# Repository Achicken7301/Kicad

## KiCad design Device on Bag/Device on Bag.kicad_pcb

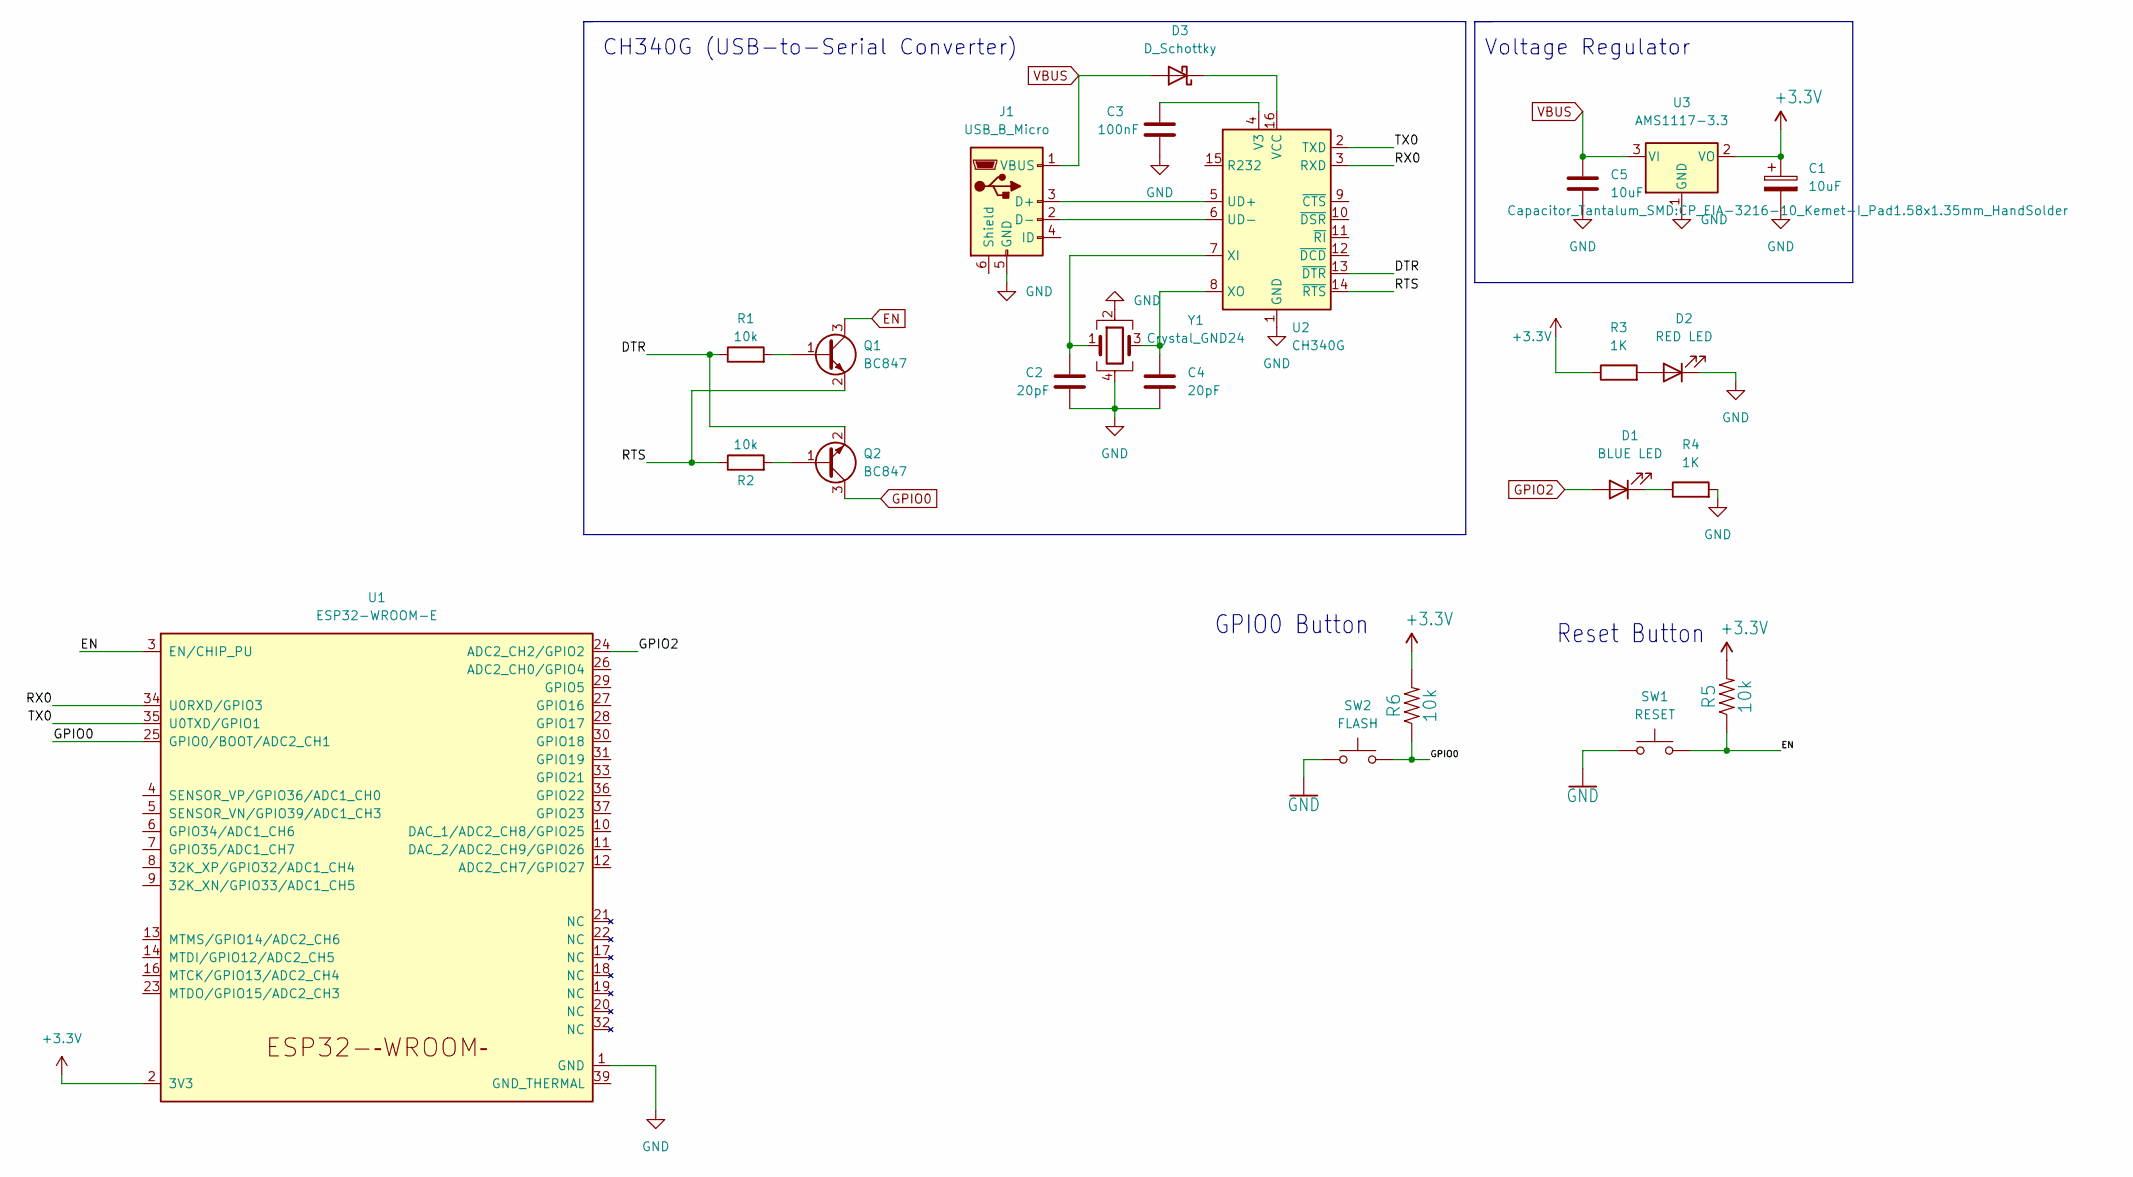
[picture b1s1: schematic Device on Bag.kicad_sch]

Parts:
C1: 10uF; CP_EIA-3216-10_Kemet-I_Pad1.58x1.35mm_HandSolder
C2, C4: 20pF; C_0805_2012Metric_Pad1.18x1.45mm_HandSolder
C3: 100nF; C_0805_2012Metric_Pad1.18x1.45mm_HandSolder
C5: 10uF; C_0805_2012Metric_Pad1.18x1.45mm_HandSolder
D1: BLUE LED; LED_0805_2012Metric_Pad1.15x1.40mm_HandSolder
D2: RED LED; LED_0805_2012Metric_Pad1.15x1.40mm_HandSolder
D3: D_Schottky; D_SMA_Handsoldering
J1: USB_B_Micro; USB_Micro-B_Molex-105017-0001
Q1, Q2: BC847; SOT-23
R1, R2, R5, R6: 10k; R_0805_2012Metric_Pad1.20x1.40mm_HandSolder
R3, R4: 1K; R_0805_2012Metric_Pad1.20x1.40mm_HandSolder
SW1: RESET; SW_Push_SPST_NO_Alps_SKRK
SW2: FLASH; SW_Push_SPST_NO_Alps_SKRK
U1: ESP32-WROOM-E; ESP32-WROOM-32E
U2: CH340G; SOIC-16_3.9x9.9mm_P1.27mm
U3: AMS1117-3.3; SOT-223-3_TabPin2
Y1: Crystal_GND24; Crystal_SMD_5032-4Pin_5.0x3.2mm

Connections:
/DTR: Q2.2 (E), R1.1, U2.13 (~DTR)
/RTS: Q1.2 (E), R2.1, U2.14 (~RTS)
/RX0: U1.34 (U0RXD/GPIO3), U2.3 (RXD)
/TX0: U1.35 (U0TXD/GPIO1), U2.2 (TXD)
EN: Q1.3 (C), R5.1, SW1.2, U1.3 (EN/CHIP_PU)
GND: C1.2, C2.2, C3.2, C4.2, C5.2, D2.1 (K), J1.5 (GND), R4.2, SW1.1, SW2.1, U1.1 (GND), U1.15 (GND), U1.38 (GND), U2.1 (GND), U3.1 (GND), Y1.2, Y1.4
GPIO0: Q2.3 (C), R6.1, SW2.2, U1.25 (GPIO0/BOOT/ADC2_CH1)
GPIO2: D1.2 (A), U1.24 (ADC2_CH2/GPIO2)
unnamed: C2.1, U2.7 (XI), Y1.1
unnamed: C3.1, U2.4 (V3)
unnamed: C4.1, U2.8 (XO), Y1.3
unnamed: D1.1 (K), R4.1
unnamed: D2.2 (A), R3.2
unnamed: D3.1 (K), U2.16 (VCC)
unnamed: J1.2 (D-), U2.6 (UD-)
unnamed: J1.3 (D+), U2.5 (UD+)
unnamed: Q1.1 (B), R1.2
unnamed: Q2.1 (B), R2.2
VBUS: C5.1, D3.2 (A), J1.1 (VBUS), U3.3 (VI)

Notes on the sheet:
Reset Button
GPIO0 Button
CH340G (USB-to-Serial Converter)
Voltage Regulator

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
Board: 2 copper layers, 23 parts (0 on the bottom side), 21 nets, no tracks yet.

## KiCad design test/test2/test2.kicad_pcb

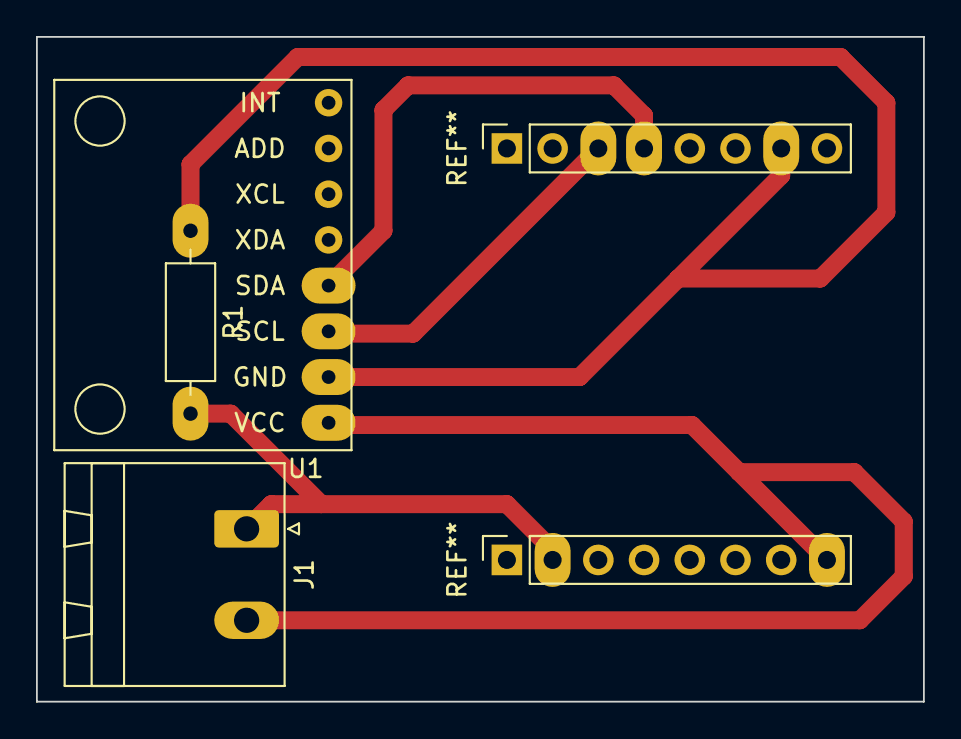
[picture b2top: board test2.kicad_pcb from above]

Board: 2 copper layers, 49.3 x 36.9 mm, 3 parts (0 on the bottom side), 3 nets.

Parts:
J1: Screw_Terminal_01x02; PhoenixContact_MSTBA_2,5_2-G-5,08_1x02_P5.08mm_Horizontal
R1: R; R_Axial_DIN0207_L6.3mm_D2.5mm_P10.16mm_Horizontal
U1: module_mpu6050

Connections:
3v3: J1.2, U1.1 (VCC)
unnamed: J1.1, R1.2
gnd: R1.1, U1.2 (GND)

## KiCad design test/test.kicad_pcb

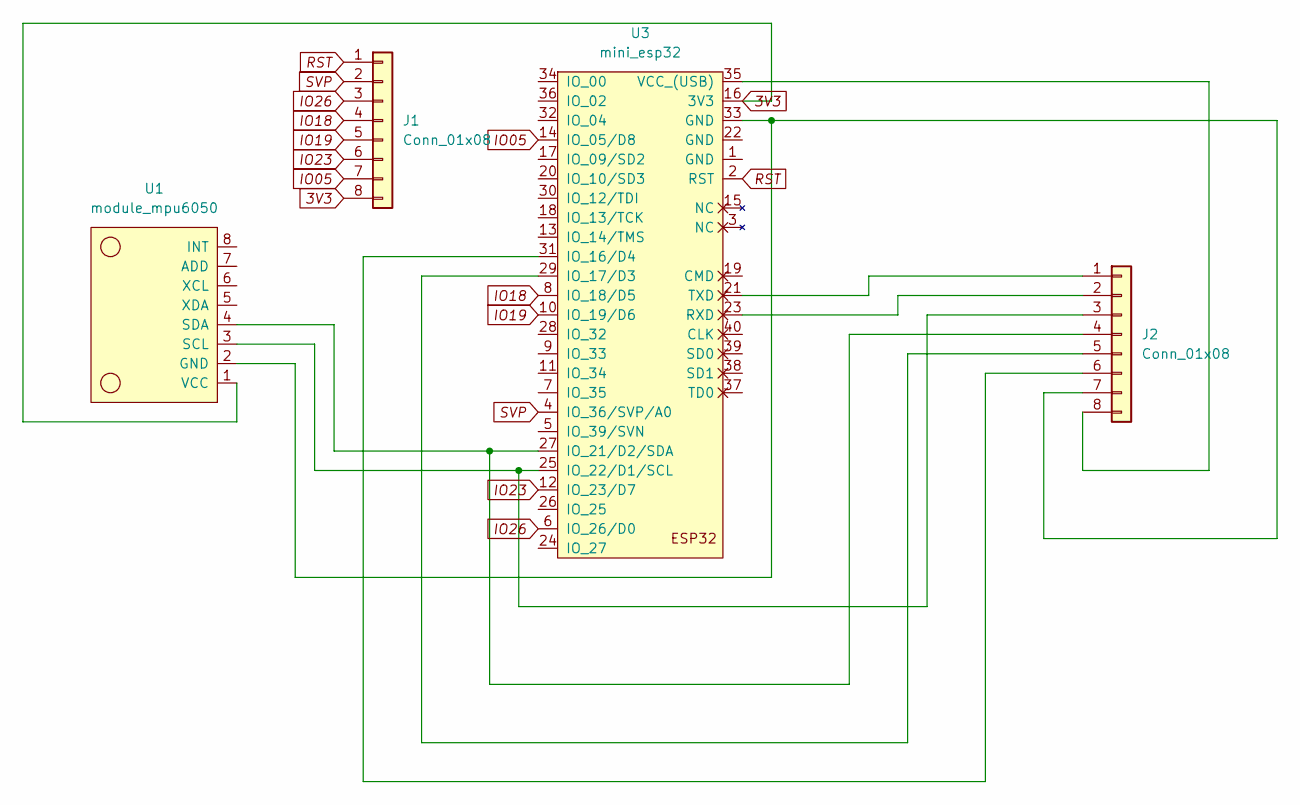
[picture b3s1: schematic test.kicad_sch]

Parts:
J1, J2: Conn_01x08; PinSocket_1x08_P2.54mm_Vertical
U1: module_mpu6050
U3: mini_esp32; ESP32_mini

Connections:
3V3: J1.8, U1.1 (VCC), U3.16 (3V3)
IO05: J1.7, U3.14 (IO_05/D8)
IO18: J1.4, U3.8 (IO_18/D5)
IO19: J1.5, U3.10 (IO_19/D6)
IO23: J1.6, U3.12 (IO_23/D7)
IO26: J1.3, U3.6 (IO_26/D0)
unnamed: J2.1, U3.21 (TXD)
unnamed: J2.2, U3.23 (RXD)
unnamed: J2.3, U1.3 (SCL), U3.25 (IO_22/D1/SCL)
unnamed: J2.4, U1.4 (SDA), U3.27 (IO_21/D2/SDA)
unnamed: J2.5, U3.29 (IO_17/D3)
unnamed: J2.6, U3.31 (IO_16/D4)
unnamed: J2.7, U1.2 (GND), U3.33 (GND)
unnamed: J2.8, U3.35 (VCC_(USB))
RST: J1.1, U3.2 (RST)
SVP: J1.2, U3.4 (IO_36/SVP/A0)

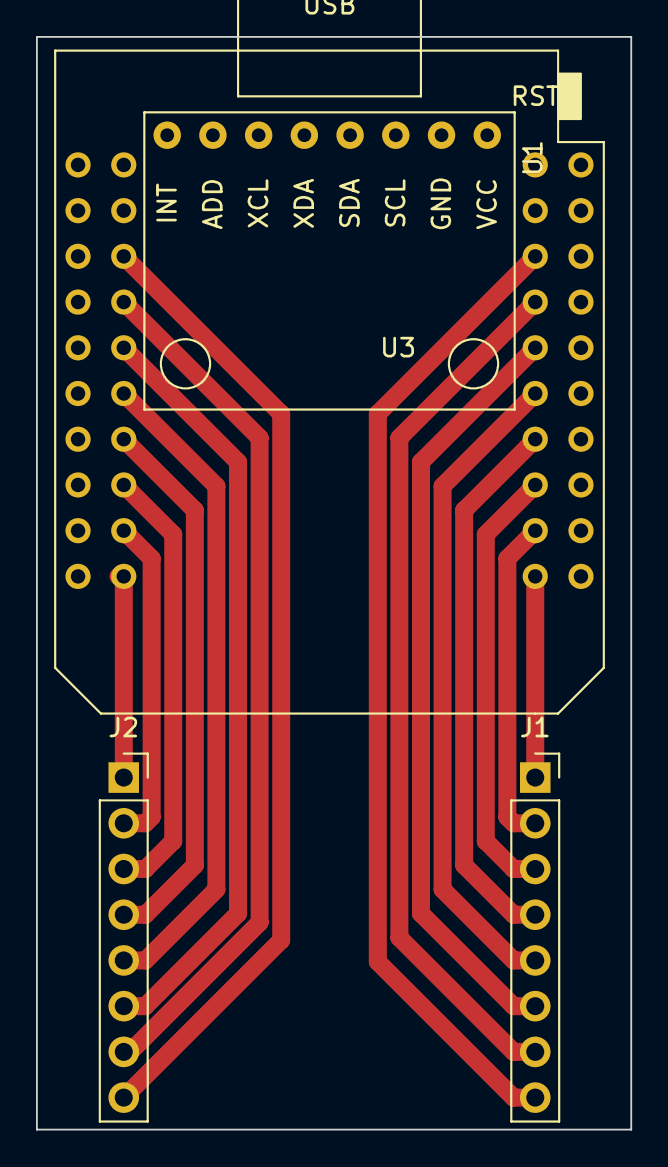
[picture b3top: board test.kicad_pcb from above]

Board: 2 copper layers, 33.0 x 60.7 mm, 4 parts (0 on the bottom side), 16 nets.

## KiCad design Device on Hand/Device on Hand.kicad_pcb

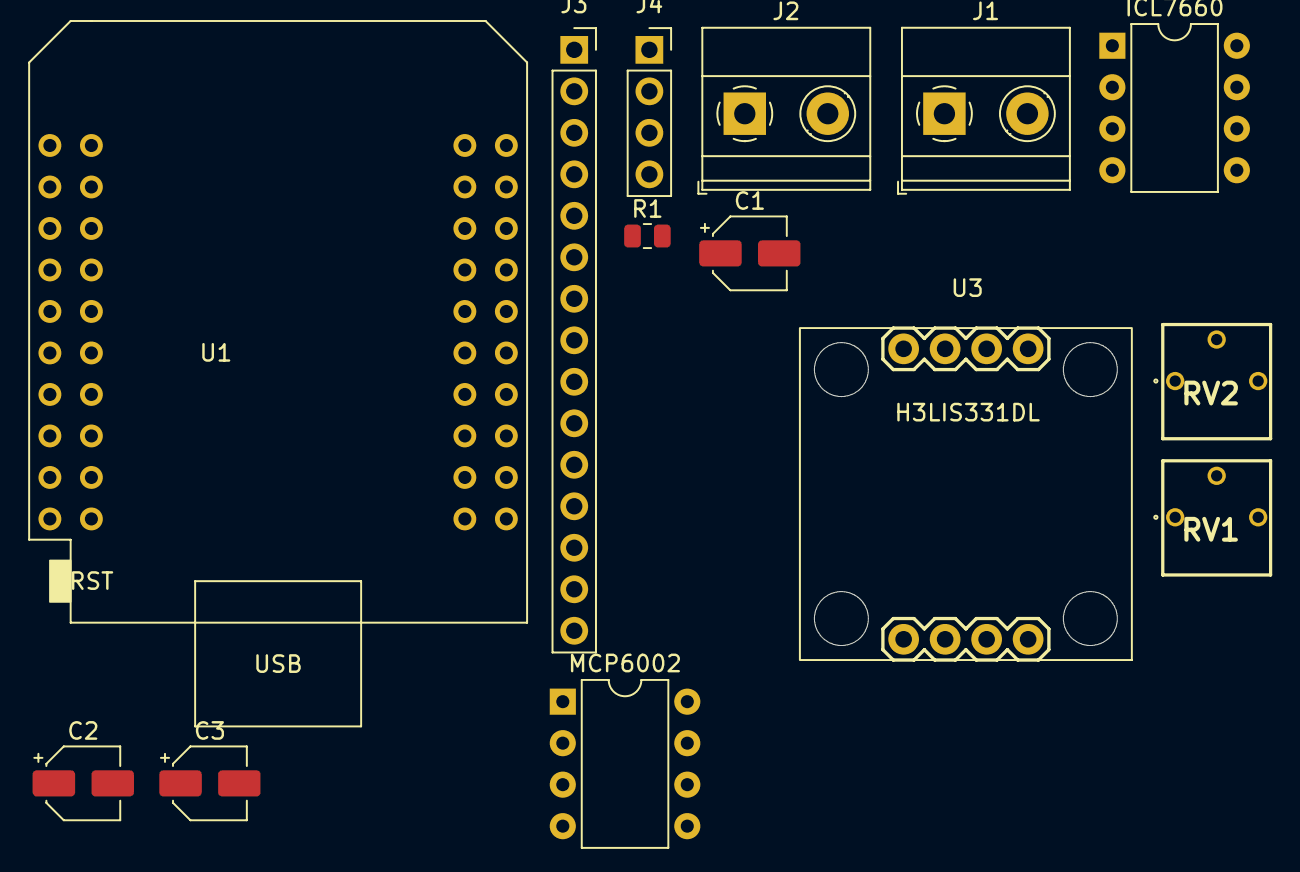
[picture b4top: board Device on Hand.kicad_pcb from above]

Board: 2 copper layers, 14 parts (0 on the bottom side), 13 nets, no tracks yet.

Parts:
C1, C2: 10uF_10V_Polarized_US; CP_Elec_4x4.5
C3: 47uF_10V_Polarized_US; CP_Elec_4x4.5
ICL7660: ICL7660; DIP-8_W7.62mm
J1, J2: Screw_Terminal_01x02; TerminalBlock_Phoenix_MKDS-1,5-2-5.08_1x02_P5.08mm_Horizont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
J3: Conn_01x15; PinSocket_1x15_P2.54mm_Vertical
J4: Screw_Terminal_01x04; PinSocket_1x04_P2.54mm_Vertical
MCP6002: MCP6002-xMC; DIP-8_W7.62mm
R1: 1k; R_0805_2012Metric
RV1: 20k_Potentiometer; 3362P_1
RV2: 100k_Potentiometer; 3362P_1
U1: mini_esp32; ESP32_mini
U3: SparkFun_SEN-14480_H3LIS331DL; SparkFun_Tri_Axis_Accel_Breakout-H3LIS331DL

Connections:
3.3Vin: J2.1, U1.35 (VCC_(USB))
3.3v: MCP6002.8 (V+), U1.16 (3V3), U3.3 (3.3V)
CS: U1.14 (IO_05/D8), U3.8 (CS)
GND: C2.1, ICL7660.3 (GND), J2.2, MCP6002.3 (+), MCP6002.4 (V-), R1.2, U1.33 (GND), U3.4 (GND)
MISO: U1.10 (IO_19/D6), U3.7 (SA0)
MOSI: U1.12 (IO_23/D7), U3.2 (SDA)
unnamed: C1.1, ICL7660.2 (CAP+)
unnamed: C1.2, ICL7660.4 (CAP-)
unnamed: C2.2, ICL7660.5 (VOUT), RV1.1
unnamed: C3.2, J1.2, MCP6002.2 (-), RV2.1
unnamed: J1.1, R1.1, RV1.2
SCL: U1.8 (IO_18/D5), U3.1 (SCL)
Vout: C3.1, MCP6002.1, RV2.2, U1.6 (IO_26/D0)

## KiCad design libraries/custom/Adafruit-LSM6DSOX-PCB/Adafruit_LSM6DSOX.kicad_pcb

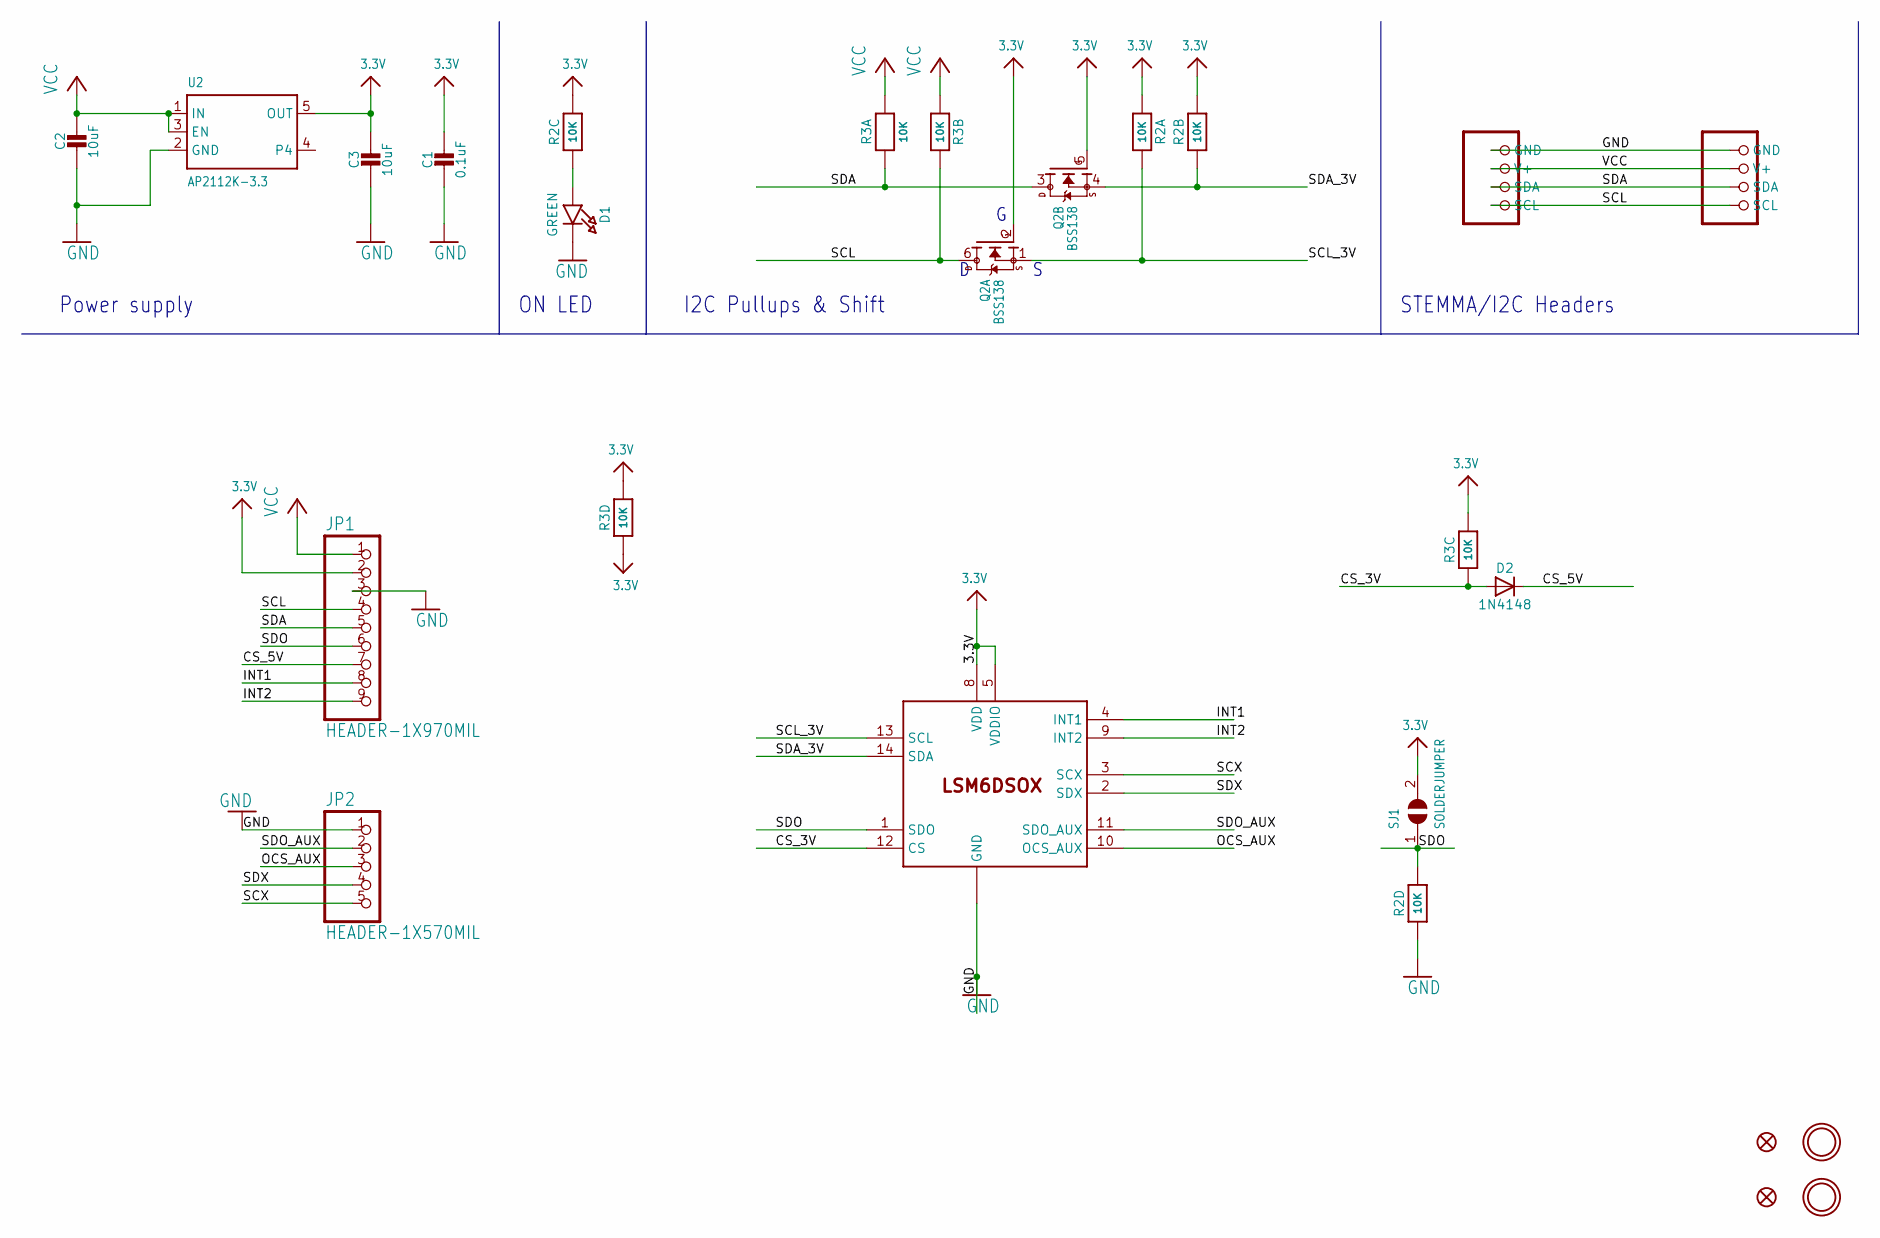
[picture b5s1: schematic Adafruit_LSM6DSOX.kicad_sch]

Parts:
C1: 0.1uF; 0603-NO
C2, C3: 10uF; 0805-NO
CONN3, CONN4: STEMMA_I2C_QT; JST_SH4
D1: GREEN; CHIPLED_0603_NOOUTLINE
D2: 1N4148; SOD-323
FID3, FID4: FIDUCIAL_1MM
JP1: HEADER-1X970MIL; 1X09_ROUND_70
JP2: HEADER-1X570MIL; 1X05_ROUND_70
Q2: BSS138; SOT363
R2, R3: 10K; RESPACK_4X0603
SJ1: SOLDERJUMPER; SOLDERJUMPER_ARROW_NOPASTE
U2: AP2112K-3.3; SOT23-5
U$1, U$17: MOUNTINGHOLE2.5; MOUNTINGHOLE_2.5_PLATED
U$2: LSM6DSOX; LGA-14L

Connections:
3.3V: C1.1, C3.1, JP1.2, Q2.2 (G), Q2.5 (G), R2.1, R2.2 (1), R2.6 (2), R3.3 (1), R3.4 (1), R3.5 (2), SJ1.2, U2.5 (OUT), U$2.5 (VDDIO), U$2.8 (VDD)
CS_3V: D2.A, R3.6 (2), U$2.12 (CS)
CS_5V: D2.C, JP1.7
GND: C1.2, C2.2, C3.2, CONN3.1 (GND), CONN4.1 (GND), D1.C, JP1.3, JP2.1, R2.4 (1), U2.2 (GND), U$2.6 (GND), U$2.7 (GND)
INT1: JP1.8, U$2.4 (INT1)
INT2: JP1.9, U$2.9 (INT2)
unnamed: D1.A, R2.3 (1)
OCS_AUX: JP2.3, U$2.10 (OCS_AUX)
SCL: CONN3.4 (SCL), CONN4.4 (SCL), JP1.4, Q2.6 (D), R3.2 (1)
SCL_3V: Q2.1 (S), R2.8 (2), U$2.13 (SCL)
SCX: JP2.5, U$2.3 (SCX)
SDA: CONN3.3 (SDA), CONN4.3 (SDA), JP1.5, Q2.3 (D), R3.1
SDA_3V: Q2.4 (S), R2.7 (2), U$2.14 (SDA)
SDO: JP1.6, R2.5 (2), SJ1.1, U$2.1 (SDO)
SDO_AUX: JP2.2, U$2.11 (SDO_AUX)
SDX: JP2.4, U$2.2 (SDX)
VCC: C2.1, CONN3.2 (V+), CONN4.2 (V+), JP1.1, R3.7 (2), R3.8 (2), U2.1 (IN), U2.3 (EN)

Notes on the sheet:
Power supply
I2C Pullups & Shift
STEMMA/I2C Headers
ON LED

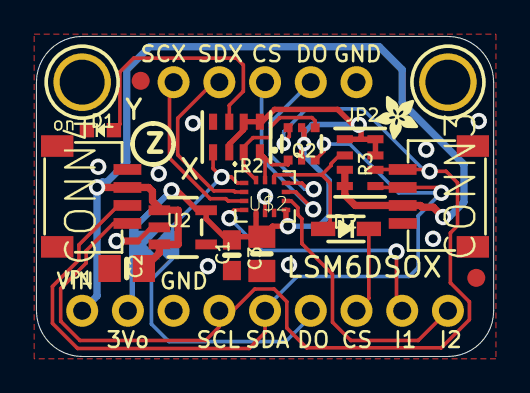
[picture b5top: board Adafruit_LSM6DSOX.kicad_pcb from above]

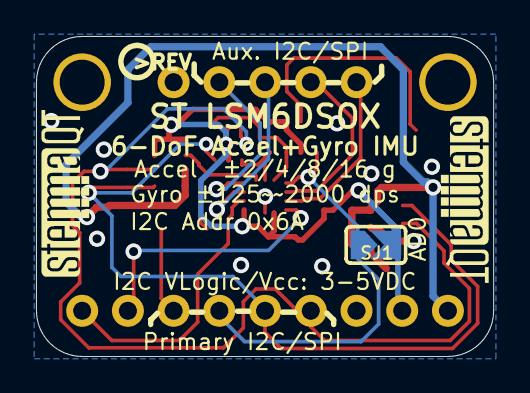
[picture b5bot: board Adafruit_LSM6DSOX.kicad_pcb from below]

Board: 2 copper layers, 25.4 x 17.8 mm, 23 parts (4 on the bottom side), 17 nets.

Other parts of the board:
U$9: ADAFRUIT_2.5MM
U$25: PCBFEAT-REV-040
U$30, U$31: STEMMAQT

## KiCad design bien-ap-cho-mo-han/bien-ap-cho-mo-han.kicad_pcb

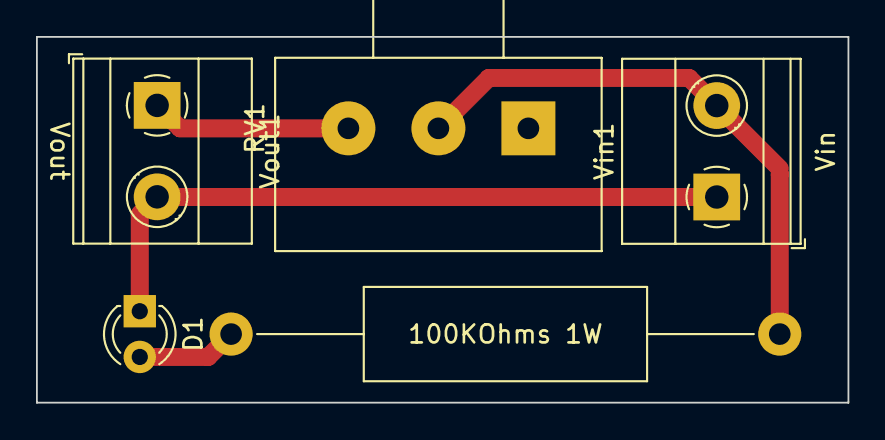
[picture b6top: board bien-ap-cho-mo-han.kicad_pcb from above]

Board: 2 copper layers, 45.1 x 20.3 mm, 5 parts (0 on the bottom side), 4 nets.

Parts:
100KOhms 1W: 100K_1W; R_Axial_DIN0516_L15.5mm_D5.0mm_P30.48mm_Horizontal
D1: LED; LED_D3.0mm
RV1: R_Potentiometer; Potentiometer_Alps_RK163_Single_Horizontal
Vin1: Screw_Terminal_01x02; TerminalBlock_Phoenix_MKDS-1,5-2-5.08_1x02_P5.08mm_Horizont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
Vout1: Screw_Terminal_01x02; TerminalBlock_Phoenix_MKDS-1,5-2-5.08_1x02_P5.08mm_Horizont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

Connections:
unnamed: D1.1 (K), Vin1.1, Vout1.2
unnamed: 100KOhms 1W.1, D1.2 (A)
unnamed: 100KOhms 1W.2, RV1.2, Vin1.2
unnamed: RV1.3, Vout1.1

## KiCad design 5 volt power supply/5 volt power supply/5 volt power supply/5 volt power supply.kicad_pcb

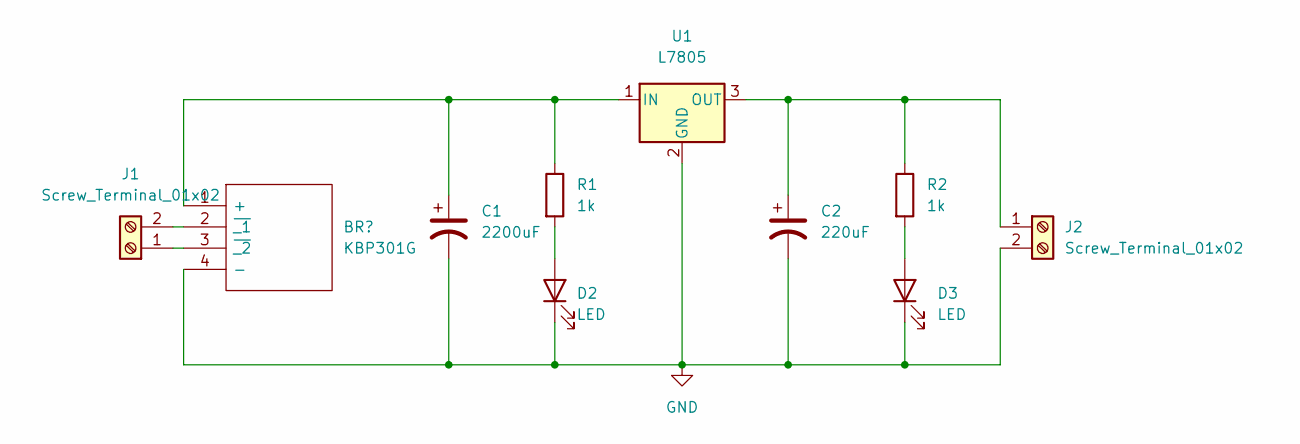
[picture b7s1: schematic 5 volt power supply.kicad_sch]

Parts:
C1: 2200uF; CP_Radial_D10.0mm_P3.50mm
C2: 220uF; CP_Radial_D10.0mm_P3.50mm
D2, D3: LED; LED_D5.0mm
J1, J2: Screw_Terminal_01x02; TerminalBlock_Phoenix_MKDS-3-2-5.08_1x02_P5.08mm_Horizontal
R1, R2: 1k; R_Axial_DIN0204_L3.6mm_D1.6mm_P7.62mm_Horizontal
U1: L7805; TO-220-3_Vertical

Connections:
GND: C1.2, C2.2, D2.1 (K), D3.1 (K), J2.2, U1.2 (GND); also elsewhere on the board
unnamed 1: C1.1, R1.1, U1.1 (IN); also elsewhere on the board
unnamed: C2.1, J2.1, R2.1, U1.3 (OUT)
unnamed: D2.2 (A), R1.2
unnamed: D3.2 (A), R2.2
unnamed 5: J1.1; also elsewhere on the board
unnamed 6: J1.2; also elsewhere on the board

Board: 2 copper layers, 10 parts (0 on the bottom side), 7 nets, no tracks yet.

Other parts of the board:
BR1: KBP301G

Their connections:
GND: BR1.4 (-); also elsewhere on the board
unnamed 1: BR1.1 (+); also elsewhere on the board
unnamed 5: BR1.3 (~_2); also elsewhere on the board
unnamed 6: BR1.2 (~_1); also elsewhere on the board

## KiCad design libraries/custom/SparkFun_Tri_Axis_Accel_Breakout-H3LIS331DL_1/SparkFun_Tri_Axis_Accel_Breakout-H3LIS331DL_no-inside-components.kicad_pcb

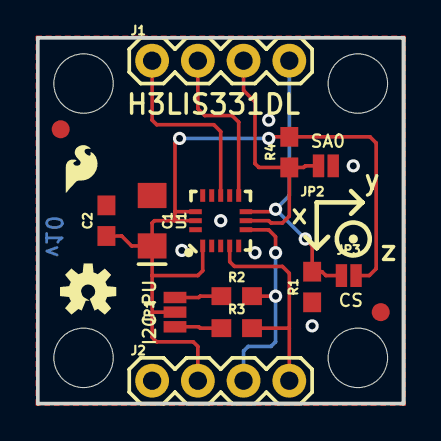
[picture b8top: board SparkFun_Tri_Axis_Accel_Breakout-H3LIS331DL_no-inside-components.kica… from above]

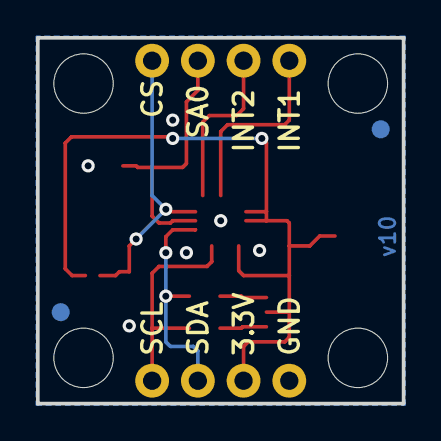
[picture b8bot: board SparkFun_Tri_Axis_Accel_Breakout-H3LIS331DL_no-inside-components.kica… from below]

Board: 4 copper layers, 20.3 x 20.3 mm, 23 parts (2 on the bottom side), 10 nets.

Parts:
C1: 10uF; EIA3216
C2: 0.1uF; 0603
FRAME1: FRAME-LETTER; CREATIVE_COMMONS
J1, J2: 1X04
JP1: JUMPER-SMT_3_2-NC_PASTE_NO-SILK; SMT-JUMPER_3_2-NC_PASTE_NO-SILK
JP2: JUMPER-SMT_2_NO_NO-SILK; SMT-JUMPER_2_NO_NO-SILK
JP3: JUMPER-SMT_2_NC_PASTE_NO-SILK; SMT-JUMPER_2_NC_PASTE_NO-SILK
JP4, JP5, JP6, JP7: FIDUCIAL1X2; FIDUCIAL-1X2
JP8, JP9, JP10, JP11: STAND-OFF
LOGO1: SFE_LOGO_FLAME.1_INCH; SFE_LOGO_FLAME_.1
LOGO2: OSHW-LOGOS; OSHW-LOGO-S
R1, R4: 10k; 0603
R2, R3: 4.7k; 0603
U1: H3LIS331DL; LGA-16-3X3

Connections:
3.3V: C1.+, C2.1, J2.2, JP1.2, JP3.2, R4.2, U1.1, U1.14, U1.15
CS: J1.4, JP3.1, R1.2, U1.8
GND: C1.-, C2.2, J2.1, JP2.1, R1.1, U1.5, U1.10, U1.12, U1.13, U1.16
INT1: J1.1, U1.11
INT2: J1.2, U1.9
unnamed: JP1.1, R3.1
unnamed: JP1.3, R2.1
SA0: J1.3, JP2.2, R4.1, U1.7
SCL: J2.4, R3.2, U1.4
SDA: J2.3, R2.2, U1.6

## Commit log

2022-11-07 update STEVAL-MK215V1 CS pin

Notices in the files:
parts and their libraries:
RELEASED UNDER THE CREATIVE COMMONS ATTRIBUTION SHARE-ALIKE 4.0 LICENSE
HTTPS://CREATIVECOMMONS.ORG/LICENSES/BY-SA/4.0
